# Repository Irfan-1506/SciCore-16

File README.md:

# SciCore-16 (v2.1) — Custom Scientific Calculator ASIC & 2-Layer Handheld PCB

A complete **RTL-to-GDSII digital ASIC** (`scicore_top` core macro on SkyWater SKY130HD 130 nm) and **custom 2-layer KiCad 10 handheld PCB** (`85 × 155 mm`, 32 tactile keys `K1–K32`) implementing a 16-bit signed Q8.8 fixed-point RPN scientific calculator, verified with **Icarus Verilog**, **Verilator (`-Wall`)**, **Yosys**, **OpenROAD Flow Scripts (SKY130HD)**, **KiCad 10 CLI**, and **ngspice-42**.

> **Project Status & Limitations:** Educational ASIC physical-design and PCB engineering project. No silicon fabrication, foundry signoff, or lab-characterized chip is claimed. All metrics below are generated directly from committed scripts and logs in this repository; items not executed locally are explicitly marked **`NOT VERIFIED`**.

---

## Visual Showcase

### 3D Handheld Calculator PCB (`85 × 155 mm`, 32 Keys, KiCad 10 Raytraced)
| Isometric 3D View | Top 3D View (32-Key Matrix) | Bottom 3D View (`B.Cu` GND & `ROW0–3`) |
| :---: | :---: | :---: |
|  |  |  |

### SKY130HD 130 nm Routed ASIC Layout (OpenROAD — `physical_design/6_final.gds`)

### SiliconForge SCMOS Block Layout (`alu16.mag` — 0 DRC, LVS Matched)

### Full-Chip IC Architecture (`scicore_asic_top`)

---

## Architecture Overview (v2.1)

```mermaid
flowchart LR
    subgraph WRAP["scicore_asic_top (QFN-64 I/O Wrapper)"]
        RST["2-FF Reset Sync<br/>(Async-Assert / Sync-Deassert)"]
        KP["keypad_scanner + keymap_decode<br/>(4x8 Matrix, 2-FF Sync, 15ms Debounce)"]
        ENT["Multi-Digit Decimal Entry<br/>(0-9, '.', DEL, ENT, CLR, STO/RCL idx)"]
        SPI["spi_result_shifter<br/>(16-bit Q8.8 SPI Output)"]
        UA["uart_debug<br/>(8N1 TX/RX @ 115200 baud)"]
        subgraph CORE["scicore_top (RPN Scientific Core)"]
            CTRL["Controller FSM<br/>(IDLE→WAIT/TAN→COMPLETE)"]
            STK["expression_stack<br/>(8x16-bit RPN Stack)"]
            REG["register_bank<br/>(4x16-bit M0..M3)"]
            ALU["alu16 / multiplier / divider<br/>(Signed Saturation)"]
            SCI["cordic [-pi,+pi] / sqrt_unit / log_exp"]
            CTRL <--> STK
            CTRL <--> REG
            CTRL --> ALU
            CTRL --> SCI
        end
        KP --> ENT --> CORE
        CORE --> SPI
        CORE --> UA
    end
```

### Key v2.1 Audit Fixes (`AUDIT_RESPONSE.md`)
- **CORDIC `[-π, +π]` range safety (`rtl/arithmetic/cordic.v`):** Added quadrant folding (`sin(π-x)=sin(x)`, `cos(π-x)=-cos(x)`) and `domain_err` for `|θ| > π` (`0x0324`), reducing full-domain error to **`<= 0.83 LSB`**.
- **High-accuracy EXP (`rtl/arithmetic/log_exp.v`):** Upgraded to 14-bit `log2(e)` (`5909/4096`), sign-magnitude 30-bit product (eliminating negative truncation bias), 32-entry Q2.14 LUT with linear interpolation, and round-to-nearest output shift (**`0.180%`** max relative error for `>= 1.0`, **`0.51 LSB`** max absolute error for `< 1.0`).
- **Explicit error & saturation policy (`rtl/top/scicore_top.v`):** Overflow in `ADD`/`SUB`/`NEG`/`MUL`/`DIV`/`EXP` saturates to `0x7FFF`/`0x8000` while setting `err_ovf`; `div_zero`, `domain_err`, `stack_overflow`, and `stack_underflow` leave the RPN stack **unchanged**.
- **Full 16-opcode map (`integration/opcodes.csv`):** Added `0xE = TAN` (micro-sequenced `CORDIC → DIV`) and `0xF = PUSH_PI` (`0x0324`); `STO`/`RCL` register index comes from the user digit key (`M0..M3`).
- **Single-source-of-truth keymap (`integration/keymap.csv` → `scripts/gen_keymap.py` → `rtl/input/keymap_decode.v`):** CI-verified 1-to-1 match with all 32 PCB switches `K1–K32`.
- **Honest I/O peripherals:**
  - `rtl/output/spi_result_shifter.v`: Shifts the raw 16-bit Q8.8 result over SPI (`disp_clk`, `disp_mosi`, `disp_cs`, `disp_dc`, `disp_rst`, `disp_bl`) to an external display bridge/MCU. *(A standalone 128×64 ST7567 framebuffer/font controller is intentionally not implemented on-die.)*
  - `rtl/output/uart_debug.v`: Full 8N1 UART TX (`115200` baud @ `10 MHz`, transmitting `"XXXX E\r\n"`) and 2-FF synchronized 8N1 RX receiver.
- **PCB & Power Simulation:** Removed obsolete `J2` header, fixed `D1`/`D2` LED polarity (180° forward-biased), assigned `H1–H4` board-only mounting holes, synced BOM/Schematic/PCB (51 components), added `330 Ω` (`5.45 mA`) bleed resistor to `power_network.cir` for AMS1117-1.8 minimum load, and committed real `ngspice-42` + `kicad-cli` reports.

---

## Command Protocol (`integration/opcodes.csv`)

RPN stack commands on `cmd_op[3:0]` (pulsed with `cmd_valid = 1` when `busy == 0`; `result` and `err_flags[4:0]` = `{stack_overflow, stack_underflow, div_zero, domain_err, arith_overflow}` are valid when `done == 1`):

| `cmd_op` | Mnemonic | Arity | Error Policy | Description |
| :---: | :--- | :---: | :--- | :--- |
| `0x0` | `PUSH` | `0 → 1` | Stack unchanged on `stack_ovf` | Push `cmd_imm[15:0]` onto stack |
| `0x1` | `CLEAR` | `N → 0` | Clears all error flags | Reset stack pointer & error flags |
| `0x2` / `0x3` | `ADD` / `SUB` | `2 → 1` | Saturate (`0x7FFF`/`0x8000`) on `ovf` | Signed Q8.8 `nos ± tos` |
| `0x4` / `0x5` | `MUL` / `DIV` | `2 → 1` | Saturate on `ovf`; stack unchanged on `div_zero` | 16-cyc `nos * tos` / 24-cyc `nos / tos` |
| `0x6` | `NEG` | `1 → 1` | Saturate `-128.0 → +127.996` on `ovf` | Signed negate `-tos` |
| `0x7` | `SQRT` | `1 → 1` | Stack unchanged on `domain_err` (`tos < 0`) | 12-cyc restoring `sqrt(tos)` |
| `0x8` / `0x9` | `SIN` / `COS` | `1 → 1` | Stack unchanged on `domain_err` (`|tos| > π`) | 12-iter CORDIC over `[-π, +π]` |
| `0xA` / `0xB` | `LN` / `EXP` | `1 → 1` | Stack unchanged on `ln(<=0)`; saturate `exp` ovf | Piecewise-linear LUT `ln` / 32-LUT `exp` |
| `0xC` / `0xD` | `STO` / `RCL` | `1→1` / `0→1` | Stack unchanged on `udf`/`ovf` | Store/Recall `M[cmd_imm[1:0]]` |
| `0xE` | `TAN` | `1 → 1` | Stack unchanged on `domain_err` / `cos==0` | Micro-sequenced `CORDIC → DIV` |
| `0xF` | `PUSH_PI` | `0 → 1` | Stack unchanged on `stack_ovf` | Push `π` (`0x0324`, `3.140625`) |

---

## Measured Results (From Committed Logs & Reports)

### 1. Exhaustive Numerical Accuracy (`verification/golden_model.py`, seed `20261121`)
Source: [`documentation/numerical_accuracy_report.md`](documentation/numerical_accuracy_report.md)

| Unit & Domain | Samples Tested | Max Abs Error | Mean Abs Error | RMS Error | Max Error (Q8.8 LSB) |
| :--- | :---: | :---: | :---: | :---: | :---: |
| `multiplier` (stratified non-overflow) | 8,096 | `0.00195` | `0.00097` | `0.00112` | **`0.50 LSB`** |
| `divider` (stratified non-overflow) | 9,991 | `0.00391` | `0.00195` | `0.00225` | **`1.00 LSB`** |
| `cordic sin(x)` (`[-π, +π]`, exhaustive) | 1,609 | `0.00323` | `0.00096` | `0.00116` | **`0.83 LSB`** |
| `cordic cos(x)` (`[-π, +π]`, exhaustive) | 1,609 | `0.00291` | `0.00097` | `0.00116` | **`0.75 LSB`** |
| `sqrt_unit` (`[0, 127.996]`, exhaustive) | 32,768 | `0.00391` | `0.00196` | `0.00226` | **`1.00 LSB`** |
| `log_exp ln(x)` (`[1/256, 127.996]`, exhaustive) | 32,767 | `0.00648` | `0.00160` | `0.00199` | **`1.66 LSB`** |
| `log_exp exp(x)` (`[-5.55, +4.85]`, exhaustive) | 2,663 | `0.03647` | `0.00242` | `0.00505` | **`9.34 LSB`** (`0.180%` rel `>=1.0`, `0.51 LSB` `<1.0`) |

### 2. RTL Verification & Lint (`scripts/run_tests.sh`, `scripts/run_lint.sh`)
- **Icarus Verilog 12.0 (`-g2001 -Wall`):** **7 / 7 self-checking testbenches PASS** (`tb_m1`, `tb_regbank`, `tb_m2` 512/512 golden vectors, `tb_m3` 114/114 CORDIC vectors, `tb_m4` 292/292 SQRT/LN/EXP vectors, `tb_top` all 16 opcodes + error policies, `tb_asic_top` multi-digit entry `12.5*3=37.5`, `sqrt(2)`, `sin(0.5)`, `STO/RCL M2`, bounce rejection).
- **Verilator 5.020 (`--lint-only -Wall`):** **0 warnings / 0 errors** on both `scicore_top` and `scicore_asic_top`.
- **Yosys (`check -assert`):** **0 latches**, **0 hierarchy/synthesis errors** on both `scicore_top` and `scicore_asic_top`.

### 3. SKY130HD Core Macro Physical Design (`scicore_top`, OpenROAD Flow Scripts)
Sources: [`physical_design/reports/orfs_run.log`](physical_design/reports/orfs_run.log), [`physical_design/reports/final_sta_power.rpt`](physical_design/reports/final_sta_power.rpt)
- **Scope:** `scicore_top` core macro only (no I/O pad ring; `scicore_asic_top` P&R is **`NOT VERIFIED`**).
- **Tools:** `openroad/orfs:latest` (Yosys `0.68+post`, OpenROAD, KLayout `def2stream.py`), SkyWater `sky130hd`, `tt_025C_1v80` typical corner only (SS/FF multi-corner signoff **`NOT VERIFIED`**).
- **Die / Core / Cell Area:** `394.34 × 394.34 µm` (`0.1555 mm²` die), `152,441.20 µm²` core, `67,486 µm²` design cell area (`44%` utilization).
- **Routing DRC & Antenna:** **0 detailed-route DRC violations** (`DRT-0199`), **0 antenna violations** after 2 antenna diodes inserted.
- **Post-Route OpenSTA Timing (`10 MHz` / `100 ns`, `tt_025C_1v80`):**
  - Setup: `WNS = 0.00 ns`, `TNS = 0.00 ns`, **Worst Setup Slack = `+73.41 ns`** (arrival `26.72 ns`).
  - Hold: **Worst Hold Slack = `-0.0083 ns` (`-8.3 ps`, `VIOLATED`)** on self-loop `u_div.divisor[12]` under `0.5 ns` hold uncertainty — transparently documented for follow-up buffer repair.
- **Vectorless Power & IR Drop (OpenSTA default activity, NOT VCD-annotated):** `0.8695 mW` total (`0.5375 mW` internal, `0.3320 mW` switching, `30.6 nW` leakage); PDNSim worstcase IR drop `18.5 µV` (VDD) / `19.2 µV` (VSS).
- **GDSII & Foundry Signoff:** `physical_design/6_final.gds` (`9.3 MB`, 0 orphan cells). External Magic/KLayout foundry DRC & Netgen LVS on `6_final.gds`: **`NOT VERIFIED`**.

### 4. Custom 2-Layer Handheld PCB (`85 × 155 mm`) & `ngspice-42` Power Simulation
Sources: [`pcb/scicore16_pcb.drc_report.json`](pcb/scicore16_pcb.drc_report.json), [`pcb/scicore16_pcb.erc_report.json`](pcb/scicore16_pcb.erc_report.json), [`pcb/simulation/power_network.log`](pcb/simulation/power_network.log)
- **Form Factor & BOM:** `85 × 155 mm` 2-layer handheld board, **51 components** (`U1–U3`, `Y1`, `SW1`, `K1–K32`, `C1–C6`, `R1–R3`, `D1–D2`, `J1`, `J3`, `J4`) + 4× `H1–H4` M3 mounting holes. `BOM == Schematic == PCB` verified by `scripts/check_consistency.py`.
- **KiCad 10.0.6 DRC (`--refill-zones --schematic-parity`):** **0 DRC errors**, **0 unconnected items** (8 warnings; 48 informational `U1` NC-pin parity notices).
- **Behavioral Power Simulation (`ngspice-42`, `pcb/simulation/power_network.cir`):**
  - Note: LDOs `U2`/`U3` use behavioral dropout+resistance sources (not vendor transistor SPICE models); includes `330 Ω` (`5.45 mA`) bleed resistor on `1.8 V` for AMS1117-1.8 minimum load.
  - Measured: `v3v3_steady = 3.2970 V`, `v1v8_steady = 1.7993 V`, `v1v8_min_droop = 1.7969 V` (`2.40 mV` / `0.13%` droop under `20 mA` load step), `t_reset_release = 0.725 ms`.

---

## Reproducing All Checks

```bash
# Run golden model, all 7 testbenches, Verilator -Wall, Yosys latch check, and cross-artifact consistency check:
make all

# Individual targets:
make report   # python3 verification/golden_model.py
make test     # bash scripts/run_tests.sh
make lint     # bash scripts/run_lint.sh
make check    # python3 scripts/check_consistency.py
make orfs     # bash scripts/run_orfs.sh (requires Docker + openroad/orfs:latest)
```

License: [MIT](LICENSE)

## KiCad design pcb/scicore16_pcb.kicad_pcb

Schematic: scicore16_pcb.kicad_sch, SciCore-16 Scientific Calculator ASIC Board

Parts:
C1, C2, C3: 10uF; C_0805_2012Metric
C4, C5, C6: 100nF; C_0805_2012Metric
D1: BUSY_GRN; LED_0805_2012Metric
D2: ERR_RED; LED_0805_2012Metric
J1: USB_5V_IN; PinHeader_1x02_P2.54mm_Vertical
J3: LCD_128x64_SPI; PinHeader_1x08_P2.54mm_Vertical
J4: UART_DEBUG; PinHeader_1x04_P2.54mm_Vertical
K1: SIN; SW_SPST_TL3342
K2: COS; SW_SPST_TL3342
K3: TAN; SW_SPST_TL3342
K4: SQRT; SW_SPST_TL3342
K5: LN; SW_SPST_TL3342
K6: EXP; SW_SPST_TL3342
K7: NEG; SW_SPST_TL3342
K8: PI; SW_SPST_TL3342
K9: STO; SW_SPST_TL3342
K10: RCL; SW_SPST_TL3342
K11: CLR; SW_SPST_TL3342
K12: DEL; SW_SPST_TL3342
K13: 7; SW_SPST_TL3342
K14: 8; SW_SPST_TL3342
K15: 9; SW_SPST_TL3342
K16: /; SW_SPST_TL3342
K17: 4; SW_SPST_TL3342
K18: 5; SW_SPST_TL3342
K19: 6; SW_SPST_TL3342
K20: *; SW_SPST_TL3342
K21: 1; SW_SPST_TL3342
K22: 2; SW_SPST_TL3342
K23: 3; SW_SPST_TL3342
K24: -; SW_SPST_TL3342
K25: 0; SW_SPST_TL3342
K26: .; SW_SPST_TL3342
K27: ENT; SW_SPST_TL3342
K28: +; SW_SPST_TL3342
K29: 2ND; SW_SPST_TL3342
K30: RAD; SW_SPST_TL3342
K31: MEM; SW_SPST_TL3342
K32: =; SW_SPST_TL3342
R1: 10k; R_0805_2012Metric
R2, R3: 1k; R_0805_2012Metric
SW1: RESET_N; SW_SPST_TL3342
U1: SciCore-16_ASIC; QFN-64-1EP_9x9mm_P0.5mm_EP4.7x4.7mm
U2: AMS1117-3.3; SOT-223-3_TabPin2
U3: AMS1117-1.8; SOT-223-3_TabPin2
Y1: 10MHz_OSC; Oscillator_SMD_Abracon_ASE-4Pin_3.2x2.5mm

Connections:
/+1V8: C3.1, U1.17, U3.2
/+3V3: C2.1, C4.1, C5.1, J3.1, J4.1, R1.1, U1.1, U2.2, U3.3, Y1.4 (Vdd)
/+5V: C1.1, J1.1, U2.3
/BUSY: R2.1, U1.45
/BUSY_LED: D1.2 (A), R2.2
/CLK_10M: U1.5, Y1.3 (OUT)
/COL0: K1.1, K2.1, K3.1, K4.1, U1.24
/COL1: K5.1, K6.1, K7.1, K8.1, U1.25
/COL2: K9.1, K10.1, K11.1, K12.1, U1.26
/COL3: K13.1, K14.1, K15.1, K16.1, U1.27
/COL4: K17.1, K18.1, K19.1, K20.1, U1.28
/COL5: K21.1, K22.1, K23.1, K24.1, U1.29
/COL6: K25.1, K26.1, K27.1, K28.1, U1.30
/COL7: K29.1, K30.1, K31.1, K32.1, U1.31
/DISP_BL: J3.8, U1.51
/DISP_CLK: J3.3, U1.56
/DISP_CS: J3.5, U1.54
/DISP_DC: J3.6, U1.53
/DISP_MOSI: J3.4, U1.55
/DISP_RST: J3.7, U1.52
/ERROR: R3.1, U1.44
/ERR_LED: D2.2 (A), R3.2
/GND: C1.2, C2.2, C3.2, C4.2, C5.2, C6.2, D1.1 (K), D2.1 (K), J1.2, J3.2, J4.2, SW1.2, U1.65, U2.1, U3.1, Y1.2 (GND)
/RESET_N: C6.1, R1.2, SW1.1, U1.6
/ROW0: K1.2, K5.2, K9.2, K13.2, K17.2, K21.2, K25.2, K29.2, U1.20
/ROW1: K2.2, K6.2, K10.2, K14.2, K18.2, K22.2, K26.2, K30.2, U1.21
/ROW2: K3.2, K7.2, K11.2, K15.2, K19.2, K23.2, K27.2, K31.2, U1.22
/ROW3: K4.2, K8.2, K12.2, K16.2, K20.2, K24.2, K28.2, K32.2, U1.23
/UART_RX: J4.4, U1.40
/UART_TX: J4.3, U1.41

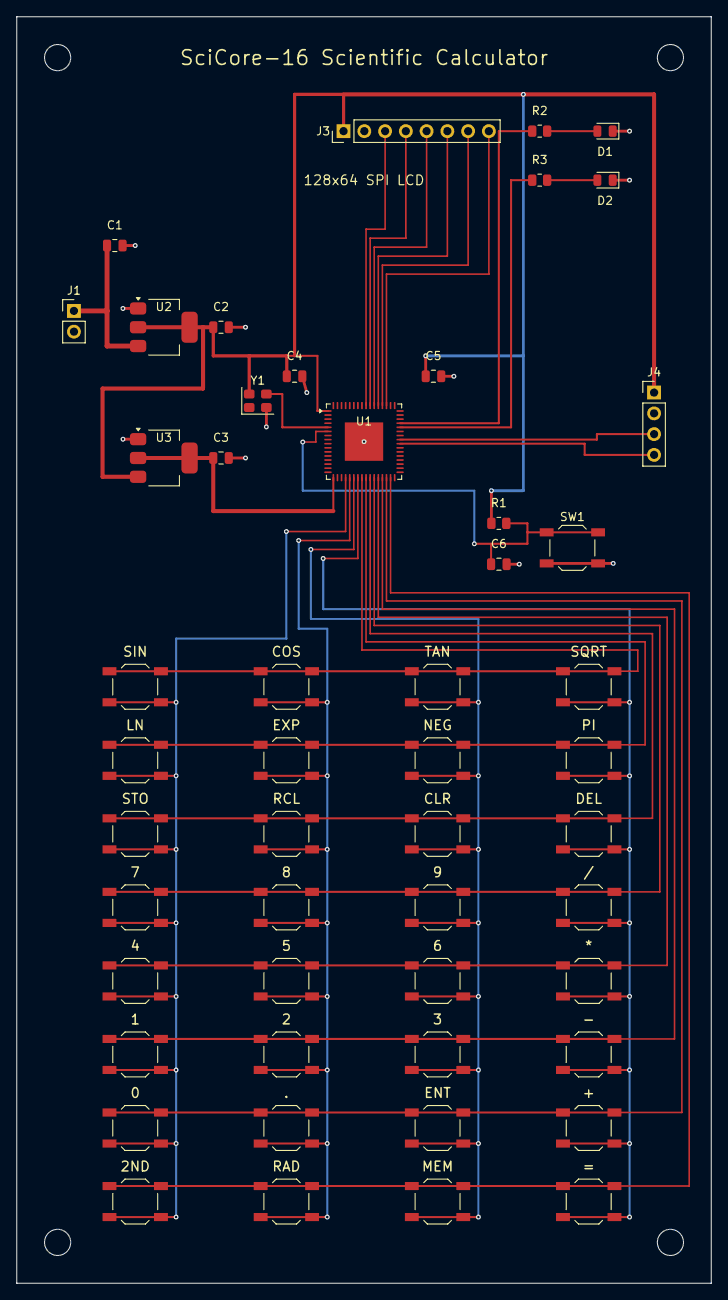
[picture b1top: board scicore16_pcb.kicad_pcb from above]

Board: 2 copper layers, 85.0 x 155.0 mm, 55 parts (0 on the bottom side), 30 nets.

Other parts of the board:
H1, H2, H3, H4: MountingHole; MountingHole_3.2mm_M3

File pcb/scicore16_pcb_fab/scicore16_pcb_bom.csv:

"Refs","Value","Footprint","Qty","DNP"
"C1","10uF","Capacitor_SMD:C_0805_2012Metric","1",""
"C2","10uF","Capacitor_SMD:C_0805_2012Metric","1",""
"C3","10uF","Capacitor_SMD:C_0805_2012Metric","1",""
"C4","100nF","Capacitor_SMD:C_0805_2012Metric","1",""
"C5","100nF","Capacitor_SMD:C_0805_2012Metric","1",""
"C6","100nF","Capacitor_SMD:C_0805_2012Metric","1",""
"D1","BUSY_GRN","LED_SMD:LED_0805_2012Metric","1",""
"D2","ERR_RED","LED_SMD:LED_0805_2012Metric","1",""
"J1","USB_5V_IN","Connector_PinHeader_2.54mm:PinHeader_1x02_P2.54mm_Vertical","1",""
"J3","LCD_128x64_SPI","Connector_PinHeader_2.54mm:PinHeader_1x08_P2.54mm_Vertical","1",""
"J4","UART_DEBUG","Connector_PinHeader_2.54mm:PinHeader_1x04_P2.54mm_Vertical","1",""
"K1","SIN","Button_Switch_SMD:SW_SPST_TL3342","1",""
"K2","COS","Button_Switch_SMD:SW_SPST_TL3342","1",""
"K3","TAN","Button_Switch_SMD:SW_SPST_TL3342","1",""
"K4","SQRT","Button_Switch_SMD:SW_SPST_TL3342","1",""
"K5","LN","Button_Switch_SMD:SW_SPST_TL3342","1",""
"K6","EXP","Button_Switch_SMD:SW_SPST_TL3342","1",""
"K7","NEG","Button_Switch_SMD:SW_SPST_TL3342","1",""
"K8","PI","Button_Switch_SMD:SW_SPST_TL3342","1",""
"K9","STO","Button_Switch_SMD:SW_SPST_TL3342","1",""
"K10","RCL","Button_Switch_SMD:SW_SPST_TL3342","1",""
"K11","CLR","Button_Switch_SMD:SW_SPST_TL3342","1",""
"K12","DEL","Button_Switch_SMD:SW_SPST_TL3342","1",""
"K13","7","Button_Switch_SMD:SW_SPST_TL3342","1",""
"K14","8","Button_Switch_SMD:SW_SPST_TL3342","1",""
"K15","9","Button_Switch_SMD:SW_SPST_TL3342","1",""
"K16","/","Button_Switch_SMD:SW_SPST_TL3342","1",""
"K17","4","Button_Switch_SMD:SW_SPST_TL3342","1",""
"K18","5","Button_Switch_SMD:SW_SPST_TL3342","1",""
"K19","6","Button_Switch_SMD:SW_SPST_TL3342","1",""
"K20","*","Button_Switch_SMD:SW_SPST_TL3342","1",""
"K21","1","Button_Switch_SMD:SW_SPST_TL3342","1",""
"K22","2","Button_Switch_SMD:SW_SPST_TL3342","1",""
"K23","3","Button_Switch_SMD:SW_SPST_TL3342","1",""
"K24","-","Button_Switch_SMD:SW_SPST_TL3342","1",""
"K25","0","Button_Switch_SMD:SW_SPST_TL3342","1",""
"K26",".","Button_Switch_SMD:SW_SPST_TL3342","1",""
"K27","ENT","Button_Switch_SMD:SW_SPST_TL3342","1",""
"K28","+","Button_Switch_SMD:SW_SPST_TL3342","1",""
"K29","2ND","Button_Switch_SMD:SW_SPST_TL3342","1",""
"K30","RAD","Button_Switch_SMD:SW_SPST_TL3342","1",""
"K31","MEM","Button_Switch_SMD:SW_SPST_TL3342","1",""
"K32","=","Button_Switch_SMD:SW_SPST_TL3342","1",""
"R1","10k","Resistor_SMD:R_0805_2012Metric","1",""
"R2","1k","Resistor_SMD:R_0805_2012Metric","1",""
"R3","1k","Resistor_SMD:R_0805_2012Metric","1",""
"SW1","RESET_N","Button_Switch_SMD:SW_SPST_TL3342","1",""
"U1","SciCore-16_ASIC","Package_DFN_QFN:QFN-64-1EP_9x9mm_P0.5mm_EP4.7x4.7mm","1",""
"U2","AMS1117-3.3","Package_TO_SOT_SMD:SOT-223-3_TabPin2","1",""
"U3","AMS1117-1.8","Package_TO_SOT_SMD:SOT-223-3_TabPin2","1",""
"Y1","10MHz_OSC","Oscillator:Oscillator_SMD_Abracon_ASE-4Pin_3.2x2.5mm","1",""
